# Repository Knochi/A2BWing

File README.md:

# A2BWing
Automotive Audio Bus Feather Wing

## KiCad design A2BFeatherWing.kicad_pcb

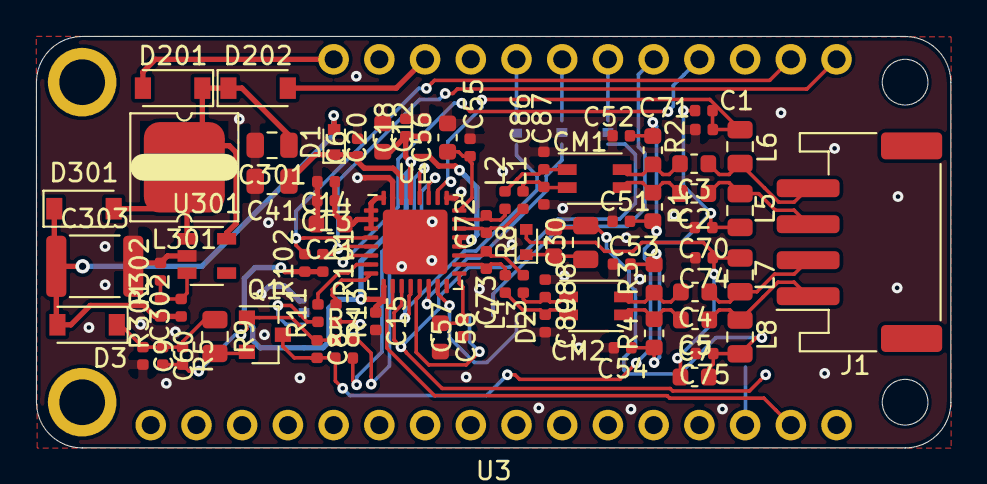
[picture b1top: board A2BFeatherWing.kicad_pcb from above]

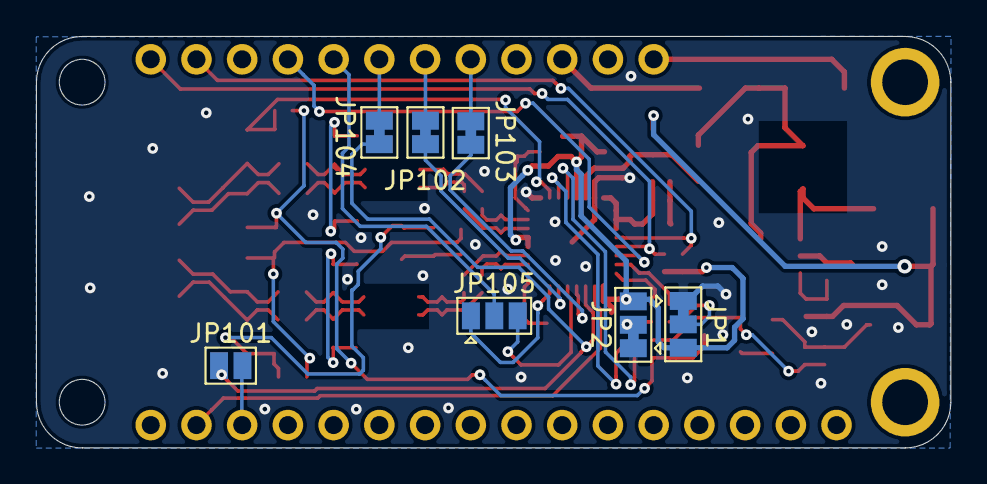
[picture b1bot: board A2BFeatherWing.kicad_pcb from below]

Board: 2 copper layers, 50.8 x 22.9 mm, 84 parts (7 on the bottom side), 58 nets.

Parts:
C1, C9, C51, C52, C53, C54, C70, C71, C74, C75: 33n; C_0402_1005Metric
C2, C3, C4, C5: 10n; C_0603_1608Metric
C6, C12, C14, C15, C55, C57: 0u1; C_0402_1005Metric
C7: 0u47; C_0603_1608Metric
C8: 3n3; C_0402_1005Metric
C13, C18: 4n7; C_0402_1005Metric
C20, C21, C56, C58: 4u7; C_0603_1608Metric
C30: 4u7; C_0805_2012Metric
C41: 10u; C_0805_2012Metric
C60: 15n; C_0402_1005Metric
C72, C73: 12p; C_0402_1005Metric
C86, C87, C88, C89: 27p; C_0402_1005Metric
C301: 2u2; C_0805_2012Metric
C302: 47p; C_0402_1005Metric
C303: 22u; C_1812_4532Metric
CM1, CM2: ACT1210-510-2P-TL00; CommonModeChoke_TDK_ACT1210
D1, D2: RB521S30; D_SOD-523
D3: SS16HE3_B/H; D_SOD-123
D201, D202, D301: MBR0520; D_SOD-123
J1: Conn_01x04_Male; JST_PH_S4B-PH-SM4-TB_1x04-1MP_P2.00mm_Horizontal
JP1, JP2: SolderJumper_3_Bridged12; SolderJumper-3_P1.3mm_Bridged12_Pad1.0x1.5mm
JP101: WS_D0; SolderJumper-2_P1.3mm_Open_Pad1.0x1.5mm
JP102: SD_D11; SolderJumper-2_P1.3mm_Bridged_Pad1.0x1.5mm
JP103: SDI_D12; SolderJumper-2_P1.3mm_Bridged_Pad1.0x1.5mm
JP104: WS_D10; SolderJumper-2_P1.3mm_Bridged_Pad1.0x1.5mm
JP105: SDO1_D9_SDI1; SolderJumper-3_P1.3mm_Open_Pad1.0x1.5mm
L1, L2, L3, L4: 180n; L_0402_1005Metric
L5, L6, L7, L8: 3u3; L_0805_2012Metric
L301: 4.7uH; L_Sumida_CR43_4.3x4.8x3.5mm
Q1: Q_PMOS_GDS; SOT-23
R1, R2, R3, R4: 120; R_0603_1608Metric
R5: 33k; R_0402_1005Metric
R6: 1k; R_0402_1005Metric
R7: 3k3; R_0402_1005Metric
R8: 4k7; R_0603_1608Metric
R9: 1r; R_0805_2012Metric
R11, R13: 10k; R_0402_1005Metric
R101, R102: 2k7; R_0402_1005Metric
R301: 60k4; R_0402_1005Metric
R302: 11k3; R_0402_1005Metric
U1: AD2428W; QFN-32-1EP_5x5mm_P0.5mm_EP3.6x3.6mm
U3: FeatherWingTemplate
U301: LT1930A; SOT-23-5

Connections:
+1V9: C13.1, C14.1, C21.1, U1.1, U1.2, U1.3, U1.32
+3V3: C12.1, C15.1, C18.1, C20.1, JP1.3, JP2.3, R101.2, R102.1, U1.9, U1.20, U1.21, U1.29
+4V: C301.1, D201.1, D202.1, L301.1, U301.5
+9V: C302.1, C303.1, D1.2, D3.2, D301.1, R301.1
+BATT: D201.2, U3.28
/A2B/A'''N: C73.2, L4.1, U1.18
/A2B/A'''P: C73.1, L3.2, U1.19
/A2B/A''N: C89.1, CM2.3, L4.2
/A2B/A''P: C88.2, CM2.1, L3.1
/A2B/A'N: C5.2, CM2.4, R4.2
/A2B/A'P: C4.2, CM2.2, R3.1
/A2B/AN: C5.1, J1.1, L8.1
/A2B/AP: C4.1, J1.2, L7.2
/A2B/B'''N: C72.2, L2.1, U1.23
/A2B/B'''P: C72.1, L1.2, U1.22
/A2B/B''N: C87.1, CM1.1, L2.2
/A2B/B''P: C86.2, CM1.3, L1.1
/A2B/B'N: C3.2, CM1.2, R2.2
/A2B/B'P: C2.2, CM1.4, R1.1
/A2B/BN: C3.1, J1.4, L6.1
/A2B/BP: C2.1, J1.3, L5.2
/A2B/IO1: R11.2, U1.7
/A2B/IO2: R13.1, U1.8
/A2B/VIN: C6.1, C41.1, D1.1, U1.30
/BCLK: U1.10, U3.15
/IRQ: U1.6, U3.20
/Power/FB: C302.2, R301.2, R302.1, U301.3
/Power/SW: D301.2, L301.2, U301.1
/SCL: R102.2, U1.4, U3.18
/SD1: JP105.2, U3.21
/SDA: R101.1, U1.5, U3.17
/SDI: JP103.1, U3.24
/SDI_0: JP103.2, U1.12
/SDI_1: JP105.3, U1.13
/SDO: JP102.1, U3.23
/SDO_0: JP102.2, U1.14
/SDO_1: JP105.1, U1.15
/SYNC: JP101.1, JP104.2, U1.11
/WS: JP104.1, U3.22
GND: C6.2, C9.2, C12.2, C13.2, C14.2, C15.2, C18.2, C20.2, C21.2, C41.2, C51.1, C52.2, C53.1, C54.2, C55.1, C56.2, C57.1, C58.2, C70.2, C71.2, C74.2, C75.2, C86.1, C87.2, C88.1, C89.2, C301.2, C303.2, JP1.1, JP2.1, R302.2, U1.25, U1.31, U1.33, U301.2
unnamed: C1.1, C8.2, C70.1, L5.1, Q1.3, R6.1
unnamed: C1.2, C71.1, L6.2, U1.26
unnamed: C7.1, C74.1, D2.2, L7.1
unnamed: C30.1, D2.1, R8.1
unnamed: C7.2, C30.2, C75.1, L8.2, R8.2
unnamed: C51.2, C52.1, R1.2, R2.1
unnamed: C53.2, C54.1, R3.2, R4.1
unnamed: C55.2, C56.1, U1.24
unnamed: C57.2, C58.1, U1.17
unnamed: C9.1, C60.1, D3.1, R5.1, R9.1
unnamed: C8.1, C60.2, Q1.1, R5.2, R7.1
unnamed: JP1.2, R11.1
unnamed: JP2.2, R13.2
unnamed: JP101.2, U3.14
unnamed: Q1.2, R9.2
unnamed: R6.2, U1.28
unnamed: R7.2, U1.27
VUSB: D202.2, U3.26

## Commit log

2019-11-29 generate BOM, update some footprints
2019-12-02 local powered slave filtnet
2019-12-02 added datasheets, power
2019-12-15 added 3d model of JST PH and CM added eco layer for silkscreen
2019-12-16 - added documentation - removed MCLK
2020-11-30 last changes
